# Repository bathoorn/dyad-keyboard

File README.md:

# Dyad

A split keyboard with a rotary encoder ring on each half — a round display
inside the left ring, a circular trackpad inside the right. Custom PCBs in
KiCad, a 3D-printed case, running QMK.

*Dyad: a pair. Two halves, two dials, two boards.*

69 keys, 32 left and 37 right, row-staggered. Bare RP2040 on each side.

---

## The idea that makes it work

"A display on top of a knob" normally means the display rotates, which needs a
slip ring or a wire loom that survives unlimited rotation.

Dyad inverts it. **The display and trackpad are static; the ring rotates around
them.** A fixed centre post rises through the bearing bore and cantilevers the
sensor above the moving parts, so no wire ever moves. Visually and
ergonomically it reads as a knob with a screen on top — electrically it's a
static part with a ring turning beneath it.

Both rings are 50 mm outside diameter, so the halves are a matched pair.

## Hardware

| | |
|---|---|
| MCU | Bare RP2040, one **shared controller module** used by both halves |
| Left pod | GC9A01 1.28" round LCD, 240×240, SPI |
| Right pod | Cirque Pinnacle TM040040, 40 mm |
| Encoders | EC11, driven by a ring gear from the rotating ring |
| Switches | MX hot-swap, Kailh sockets |
| Per-key RGB | SK6812MINI-E — footprints fitted, populated only if wanted |
| Split link | USB-C to USB-C, half-duplex serial |

Four board designs: one controller module (the only board needing an assembly
service), two asymmetric main PCBs, and two knob-module variants.

## Status

| Phase | State |
|---|---|
| 0 — Layout | **Done.** Validated against printed 1:1 mock-ups. |
| 1 — Bench bring-up | **Partial.** Toolchain, flashing, encoder and Cirque all pass. Display, ribbon-SPI, split and current tests await parts. |
| 2 — Knob mechanism | Not started. |
| 3 — KiCad | Main PCBs generated and placed; controller pin assignment and BOM settled. |
| 4 — Case | Not started. Board outlines and plate cutouts exported for it. |

The main PCBs are a **placement scaffold**, not a finished layout. DRC reports
195 violations on the left and 253 on the right, **none** electrical (shorts,
clearance, mask bridges). The 32 and 37 errors are all diode/switch courtyard
overlaps from the deliberate diode-under-switch placement; the rest is
silkscreen. Routing is incomplete, notably the angled thumb keys.

## Repository

```
docs/          PLAN.md, WORKFLOW.md, CONTROLLER.md, PHASE1.md, TOOLS.md,
               GIT.md, plus printable 1:1 mock-ups
hardware/
  interface.yaml   the contract between the PCB and case designs
  layout/          KLE source of truth, parser, pod-placement solver
  pcb-main-*/      the two main PCBs (generated)
  pcb-controller/  controller module, and the vendored RP2040 reference
  outlines/        board outlines, plate cutouts and STEP, for the case
firmware/      QMK external userspace
```

Nearly everything under `hardware/` is **generated** from the KLE layout.
Regenerate with `hardware/generate_main_pcbs.py`, `export_outlines.py` and
`export_plate.py` — see `docs/TOOLS.md` for the environment they need.

## Building the firmware

```bash
qmk config user.qmk_home=~/qmk_firmware
qmk config user.overlay_dir=$PWD/firmware
ln -sfn $PWD/firmware/keyboards/dyad ~/qmk_firmware/keyboards/dyad
qmk compile -kb dyad/split -km default
```

The symlink is required: QMK's external userspace holds keymaps and build
targets, but **not keyboards**.

`dyad/proto` and `dyad/split` are Phase 1 bring-up targets for dev boards, not
the shipping keyboard definition.

## Documentation

- **[PLAN.md](docs/PLAN.md)** — the full design, decisions and rationale
- **[WORKFLOW.md](docs/WORKFLOW.md)** — how the case and PCBs are co-designed
  without deadlocking
- **[CONTROLLER.md](docs/CONTROLLER.md)** — controller pin assignment, BOM and
  build steps
- **[PHASE1.md](docs/PHASE1.md)** — bench bring-up, with results
- **[TOOLS.md](docs/TOOLS.md)** — toolchain, and the traps found in it
- **[GIT.md](docs/GIT.md)** — feature branches, and why KiCad files change how
  git is used here

## Licence

MIT — see [LICENSE](LICENSE).

`hardware/pcb-controller/upstream/` vendors
[RP2040-designguide](https://github.com/calliah333/RP2040-designguide)
(MIT, © 2021 Sleepdealer) as a read-only reference. The key layout originates
from the *Hasukey* KLE layout.

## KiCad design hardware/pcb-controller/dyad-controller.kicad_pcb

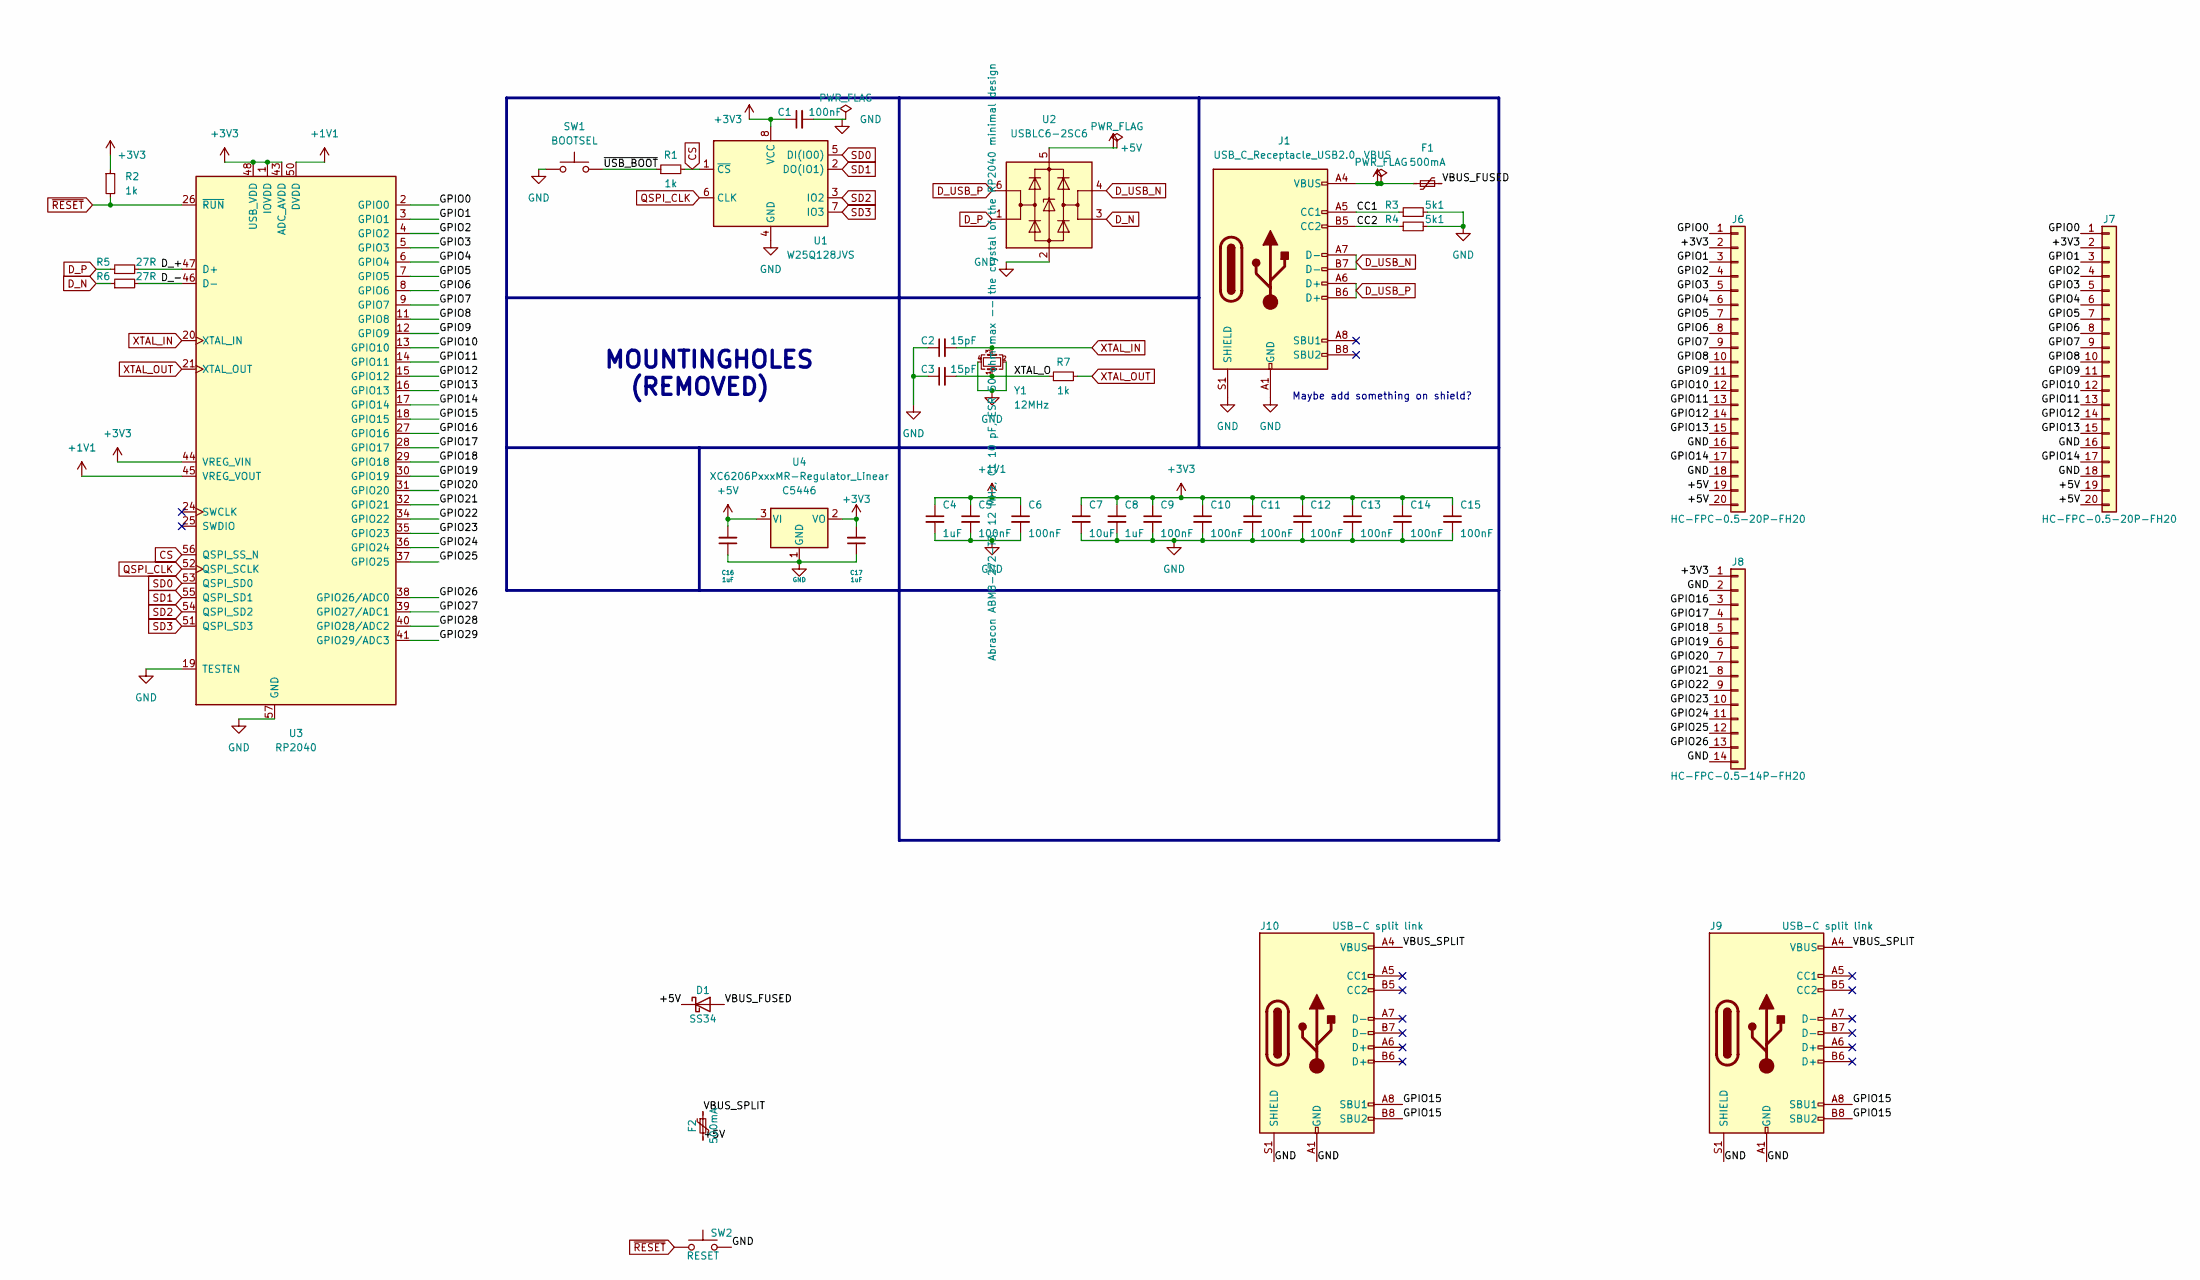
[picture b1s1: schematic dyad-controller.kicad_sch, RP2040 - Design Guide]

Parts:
C1, C5, C6, C9, C10, C11, C12, C13, C14, C15: 100nF; C_0402_1005Metric; LCSC C1525
C2, C3: 15pF; C_0402_1005Metric; LCSC C1548
C4, C8, C16, C17: 1uF; C_0402_1005Metric; LCSC C52923
C7: 10uF; C_0402_1005Metric; LCSC C15525
D1: SS34; D_SMA; LCSC C8678
F1, F2: 500mA; Fuse_1206_3216Metric; LCSC C70076
J1: USB_C_Receptacle_USB2.0; USB_C_Receptacle_HRO_TYPE-C-31-M-12; LCSC C165948
J6, J7: HC-FPC-0.5-20P-FH20; FPC-SMD_20P-P0.50_HC-FPC-0.5-20P-FH20; LCSC C19273932
J8: HC-FPC-0.5-14P-FH20; FPC-SMD_14P-P0.50_HC-FPC-0.5-14P-FH20; LCSC C19273929
J9, J10: USB-C split link; USB_C_Receptacle_HRO_TYPE-C-31-M-12; LCSC C165948
R1, R2, R7: 1k; R_0402_1005Metric; LCSC C11702
R3, R4: 5k1; R_0402_1005Metric; LCSC C25905
R5, R6: 27R; R_0603_1608Metric; LCSC C25190
SW1: BOOTSEL; SW_Push_1P1T_XKB_TS-1187A; LCSC C318884
SW2: RESET; SW_Push_1P1T_XKB_TS-1187A; LCSC C318884
U1: W25Q128JVS; SOIC-8_5.23x5.23mm_P1.27mm; LCSC C131025
U2: USBLC6-2SC6; SOT-23-6; LCSC C2827654
U3: RP2040; RP2040-QFN-56; LCSC C2040
U4: XC6206PxxxMR-Regulator_Linear; SOT-23; LCSC C5446
Y1: 12MHz; Crystal_SMD_3225-4Pin_3.2x2.5mm; LCSC C20625731

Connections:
+1V1: C4.1, C5.1, C6.1, U3.23 (DVDD), U3.45 (VREG_VOUT), U3.50 (DVDD)
+3V3: C1.1, C7.1, C8.1, C9.1, C10.1, C11.1, C12.1, C13.1, C14.1, C15.1, C17.2, J6.2, J7.2, J8.1, R2.1, U1.8 (VCC), U3.1 (IOVDD), U3.10 (IOVDD), U3.22 (IOVDD), U3.33 (IOVDD), U3.42 (IOVDD), U3.43 (ADC_AVDD), U3.44 (VREG_VIN), U3.48 (USB_VDD), U3.49 (IOVDD), U4.2 (VO)
+5V: C16.2, D1.1 (K), F2.2, J6.19, J6.20, J7.19, J7.20, U2.5 (VBUS), U4.3 (VI)
/CC1: J1.A5 (CC1), R3.1
/CC2: J1.B5 (CC2), R4.1
/D_+: R5.2, U3.47 (D+)
/D_-: R6.2, U3.46 (D-)
/GPIO0: J6.1, J7.1, U3.2 (GPIO0)
/GPIO1: J6.3, J7.3, U3.3 (GPIO1)
/GPIO2: J6.4, J7.4, U3.4 (GPIO2)
/GPIO3: J6.5, J7.5, U3.5 (GPIO3)
/GPIO4: J6.6, J7.6, U3.6 (GPIO4)
/GPIO5: J6.7, J7.7, U3.7 (GPIO5)
/GPIO6: J6.8, J7.8, U3.8 (GPIO6)
/GPIO7: J6.9, J7.9, U3.9 (GPIO7)
/GPIO8: J6.10, J7.10, U3.11 (GPIO8)
/GPIO9: J6.11, J7.11, U3.12 (GPIO9)
/GPIO10: J6.12, J7.12, U3.13 (GPIO10)
/GPIO11: J6.13, J7.13, U3.14 (GPIO11)
/GPIO12: J6.14, J7.14, U3.15 (GPIO12)
/GPIO13: J6.15, J7.15, U3.16 (GPIO13)
/GPIO14: J6.17, J7.17, U3.17 (GPIO14)
/GPIO15: J9.A8 (SBU1), J9.B8 (SBU2), J10.A8 (SBU1), J10.B8 (SBU2), U3.18 (GPIO15)
/GPIO16: J8.3, U3.27 (GPIO16)
/GPIO17: J8.4, U3.28 (GPIO17)
/GPIO18: J8.5, U3.29 (GPIO18)
/GPIO19: J8.6, U3.30 (GPIO19)
/GPIO20: J8.7, U3.31 (GPIO20)
/GPIO21: J8.8, U3.32 (GPIO21)
/GPIO22: J8.9, U3.34 (GPIO22)
/GPIO23: J8.10, U3.35 (GPIO23)
/GPIO24: J8.11, U3.36 (GPIO24)
/GPIO25: J8.12, U3.37 (GPIO25)
/GPIO26: J8.13, U3.38 (GPIO26/ADC0)
/GPIO27: U3.39 (GPIO27/ADC1)
/GPIO28: U3.40 (GPIO28/ADC2)
/GPIO29: U3.41 (GPIO29/ADC3)
/VBUS_FUSED: D1.2 (A), F1.2
/VBUS_SPLIT: F2.1, J9.A4 (VBUS), J9.A9 (VBUS), J9.B4 (VBUS), J9.B9 (VBUS), J10.A4 (VBUS), J10.A9 (VBUS), J10.B4 (VBUS), J10.B9 (VBUS)
/XTAL_O: C3.2, R7.1, Y1.1
/~USB_BOOT: R1.1, SW1.2
CS: R1.2, U1.1 (~CS), U3.56 (QSPI_SS_N)
D_N: R6.1, U2.3 (I/O2)
D_P: R5.1, U2.1 (I/O1)
D_USB_N: J1.A7 (D-), J1.B7 (D-), U2.4 (I/O2)
D_USB_P: J1.A6 (D+), J1.B6 (D+), U2.6 (I/O1)
GND: C1.2, C2.1, C3.1, C4.2, C5.2, C6.2, C7.2, C8.2, C9.2, C10.2, C11.2, C12.2, C13.2, C14.2, C15.2, C16.1, C17.1, J1.A1 (GND), J1.A12 (GND), J1.B1 (GND), J1.B12 (GND), J1.S1 (SHIELD), J6.16, J6.18, J7.16, J7.18, J8.2, J8.14, J9.A1 (GND), J9.A12 (GND), J9.B1 (GND), J9.B12 (GND), J9.S1 (SHIELD), J10.A1 (GND), J10.A12 (GND), J10.B1 (GND), J10.B12 (GND), J10.S1 (SHIELD), R3.2, R4.2, SW1.1, SW2.2, U1.4 (GND), U2.2 (GND), U3.19 (TESTEN), U3.57 (GND), U4.1 (GND), Y1.2, Y1.4; also elsewhere on the board
QSPI_CLK: U1.6 (CLK), U3.52 (QSPI_SCLK)
SD0: U1.5 (DI(IO0)), U3.53 (QSPI_SD0)
SD1: U1.2 (DO(IO1)), U3.55 (QSPI_SD1)
SD2: U1.3 (IO2), U3.54 (QSPI_SD2)
SD3: U1.7 (IO3), U3.51 (QSPI_SD3)
VBUS: F1.1, J1.A4 (VBUS), J1.A9 (VBUS), J1.B4 (VBUS), J1.B9 (VBUS)
XTAL_IN: C2.2, U3.20 (XTAL_IN), Y1.3
XTAL_OUT: R7.2, U3.21 (XTAL_OUT)
~RESET: R2.2, SW2.1, U3.26 (~RUN)

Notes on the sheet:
MOUNTINGHOLES (REMOVED)
Maybe add something on shield?

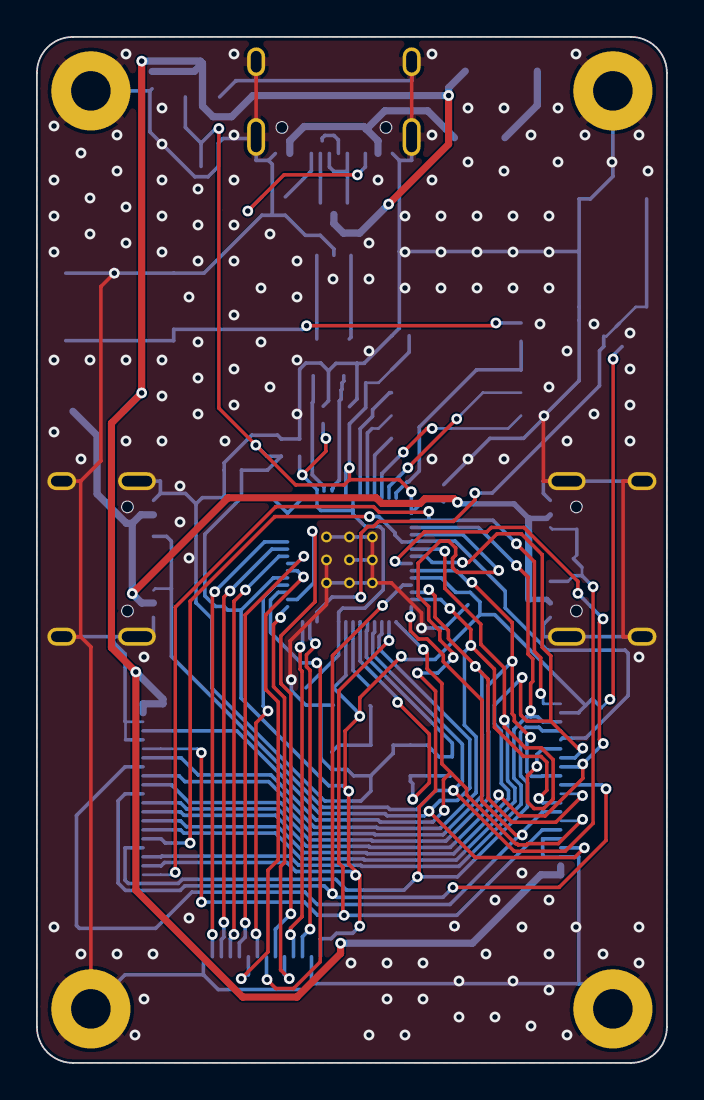
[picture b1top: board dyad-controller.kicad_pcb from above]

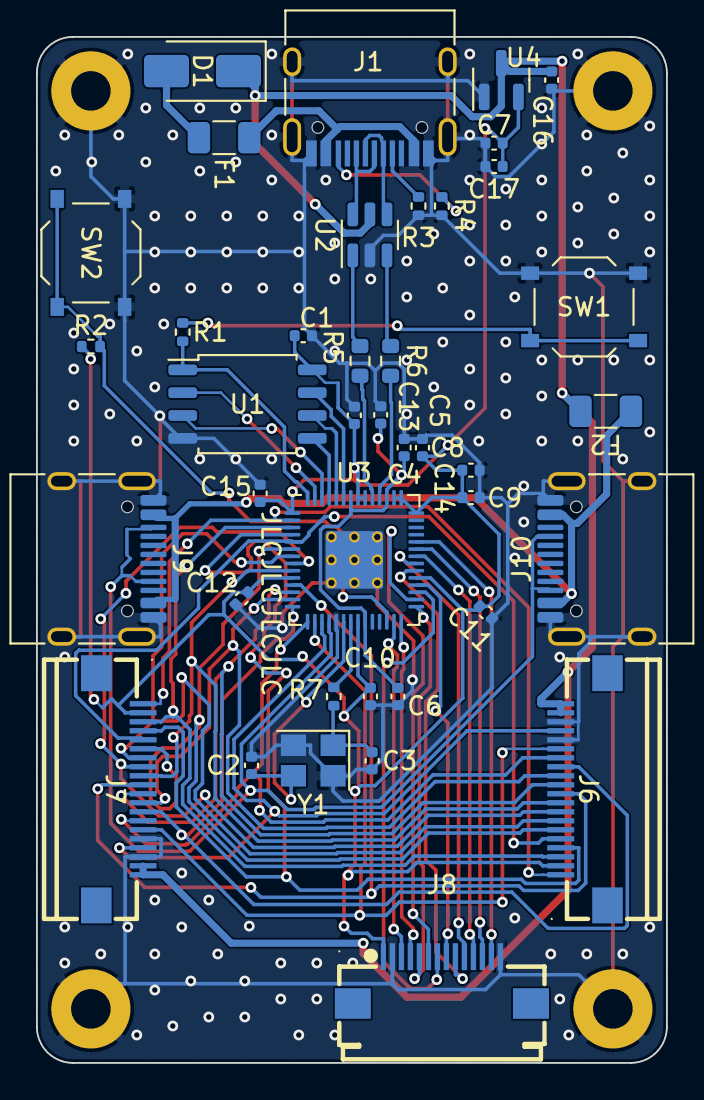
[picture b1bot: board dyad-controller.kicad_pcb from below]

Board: 2 copper layers, 35.0 x 57.0 mm, 44 parts (40 on the bottom side), 53 nets.

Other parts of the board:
H1, H2, H3, H4: MountingHole_2.2mm_M2_Pad

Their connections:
GND: H1.1, H2.1, H3.1, H4.1; also elsewhere on the board

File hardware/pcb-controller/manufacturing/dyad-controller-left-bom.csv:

Comment,Designator,Footprint,LCSC Part #
100nF,"C1,C5,C6,C9,C10,C11,C12,C13,C14,C15",C_0402_1005Metric,C1525
15pF,"C2,C3",C_0402_1005Metric,C1548
1uF,"C4,C8,C16,C17",C_0402_1005Metric,C52923
10uF,C7,C_0402_1005Metric,C15525
SS34,D1,D_SMA,C8678
500mA,"F1,F2",Fuse_1206_3216Metric,C70076
USB_C_Receptacle_USB2.0,J1,USB_C_Receptacle_HRO_TYPE-C-31-M-12,C165948
HC-FPC-0.5-20P-FH20,J6,FPC-SMD_20P-P0.50_HC-FPC-0.5-20P-FH20,C19273932
HC-FPC-0.5-14P-FH20,J8,FPC-SMD_14P-P0.50_HC-FPC-0.5-14P-FH20,C19273929
USB-C split link,J9,USB_C_Receptacle_HRO_TYPE-C-31-M-12,C165948
1k,"R1,R2,R7",R_0402_1005Metric,C11702
5k1,"R3,R4",R_0402_1005Metric,C25905
27R,"R5,R6",R_0603_1608Metric,C25190
BOOTSEL,SW1,SW_Push_1P1T_XKB_TS-1187A,C318884
RESET,SW2,SW_Push_1P1T_XKB_TS-1187A,C318884
W25Q128JVS,U1,SOIC-8_5.23x5.23mm_P1.27mm,C131025
USBLC6-2SC6,U2,SOT-23-6,C2827654
RP2040,U3,RP2040-QFN-56,C2040
XC6206PxxxMR-Regulator_Linear,U4,SOT-23,C5446
12MHz,Y1,Crystal_SMD_3225-4Pin_3.2x2.5mm,C20625731

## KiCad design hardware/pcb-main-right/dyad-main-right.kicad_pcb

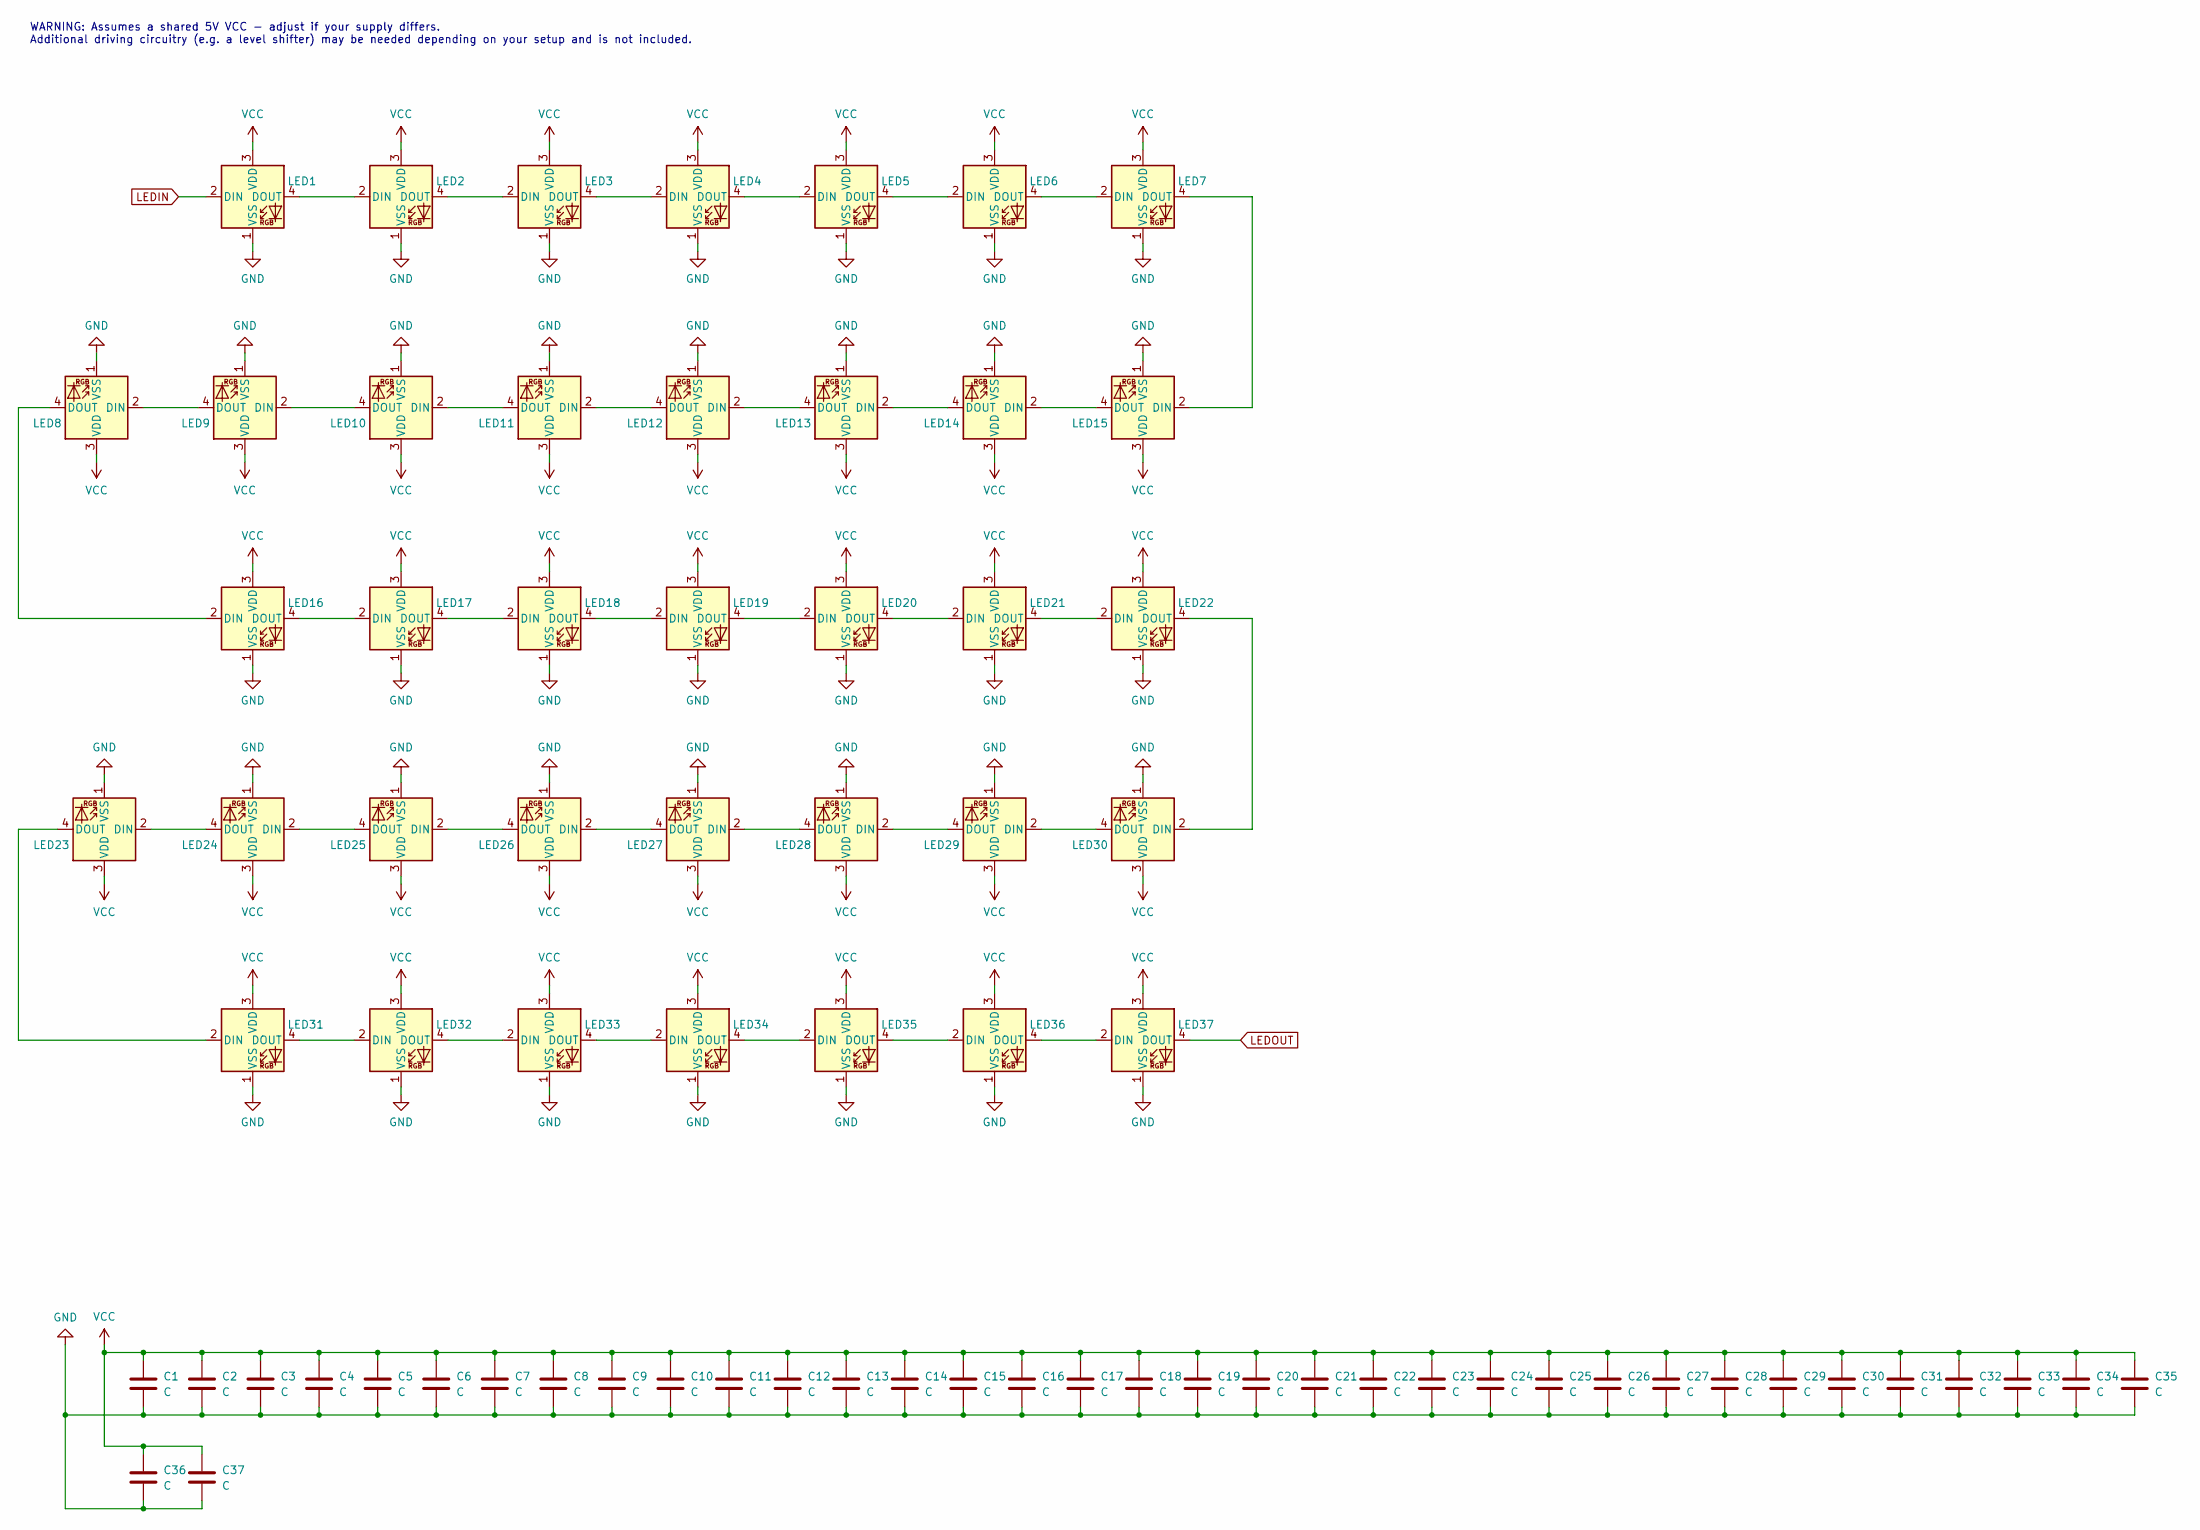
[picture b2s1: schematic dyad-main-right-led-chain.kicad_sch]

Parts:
C1, C2, C3, C4, C5, C6, C7, C8, C9, C10, C11, C12, C13, C14, C15, C16, C17, C18, C19, C20, C21, C22, C23, C24, C25, C26, C27, C28, C29, C30, C31, C32, C33, C34, C35, C36, C37: C; C_0603_1608Metric
LED1, LED2, LED3, LED4, LED5, LED6, LED7, LED8, LED9, LED10, LED11, LED12, LED13, LED14, LED15, LED16, LED17, LED18, LED19, LED20, LED21, LED22, LED23, LED24, LED25, LED26, LED27, LED28, LED29, LED30, LED31, LED32, LED33, LED34, LED35, LED36, LED37: SK6812MINI-E; LED_SK6812MINI-E_3.2x2.8mm_P1.5mm_ReverseMount

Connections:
GND: C1.2, C2.2, C3.2, C4.2, C5.2, C6.2, C7.2, C8.2, C9.2, C10.2, C11.2, C12.2, C13.2, C14.2, C15.2, C16.2, C17.2, C18.2, C19.2, C20.2, C21.2, C22.2, C23.2, C24.2, C25.2, C26.2, C27.2, C28.2, C29.2, C30.2, C31.2, C32.2, C33.2, C34.2, C35.2, C36.2, C37.2, LED1.1 (VSS), LED2.1 (VSS), LED3.1 (VSS), LED4.1 (VSS), LED5.1 (VSS), LED6.1 (VSS), LED7.1 (VSS), LED8.1 (VSS), LED9.1 (VSS), LED10.1 (VSS), LED11.1 (VSS), LED12.1 (VSS), LED13.1 (VSS), LED14.1 (VSS), LED15.1 (VSS), LED16.1 (VSS), LED17.1 (VSS), LED18.1 (VSS), LED19.1 (VSS), LED20.1 (VSS), LED21.1 (VSS), LED22.1 (VSS), LED23.1 (VSS), LED24.1 (VSS), LED25.1 (VSS), LED26.1 (VSS), LED27.1 (VSS), LED28.1 (VSS), LED29.1 (VSS), LED30.1 (VSS), LED31.1 (VSS), LED32.1 (VSS), LED33.1 (VSS), LED34.1 (VSS), LED35.1 (VSS), LED36.1 (VSS), LED37.1 (VSS); also elsewhere on the board
LEDIN: LED1.2 (DIN); also elsewhere on the board
LEDOUT: LED37.4 (DOUT)
unnamed: LED1.4 (DOUT), LED2.2 (DIN)
unnamed: LED2.4 (DOUT), LED3.2 (DIN)
unnamed: LED3.4 (DOUT), LED4.2 (DIN)
unnamed: LED4.4 (DOUT), LED5.2 (DIN)
unnamed: LED5.4 (DOUT), LED6.2 (DIN)
unnamed: LED6.4 (DOUT), LED7.2 (DIN)
unnamed: LED8.2 (DIN), LED9.4 (DOUT)
unnamed: LED10.2 (DIN), LED11.4 (DOUT)
unnamed: LED9.2 (DIN), LED10.4 (DOUT)
unnamed: LED11.2 (DIN), LED12.4 (DOUT)
unnamed: LED12.2 (DIN), LED13.4 (DOUT)
unnamed: LED13.2 (DIN), LED14.4 (DOUT)
unnamed: LED14.2 (DIN), LED15.4 (DOUT)
unnamed: LED7.4 (DOUT), LED15.2 (DIN)
unnamed: LED8.4 (DOUT), LED16.2 (DIN)
unnamed: LED16.4 (DOUT), LED17.2 (DIN)
unnamed: LED17.4 (DOUT), LED18.2 (DIN)
unnamed: LED18.4 (DOUT), LED19.2 (DIN)
unnamed: LED19.4 (DOUT), LED20.2 (DIN)
unnamed: LED20.4 (DOUT), LED21.2 (DIN)
unnamed: LED21.4 (DOUT), LED22.2 (DIN)
unnamed: LED22.4 (DOUT), LED30.2 (DIN)
unnamed: LED23.2 (DIN), LED24.4 (DOUT)
unnamed: LED23.4 (DOUT), LED31.2 (DIN)
unnamed: LED24.2 (DIN), LED25.4 (DOUT)
unnamed: LED25.2 (DIN), LED26.4 (DOUT)
unnamed: LED26.2 (DIN), LED27.4 (DOUT)
unnamed: LED27.2 (DIN), LED28.4 (DOUT)
unnamed: LED28.2 (DIN), LED29.4 (DOUT)
unnamed: LED29.2 (DIN), LED30.4 (DOUT)
unnamed: LED31.4 (DOUT), LED32.2 (DIN)
unnamed: LED32.4 (DOUT), LED33.2 (DIN)
unnamed: LED33.4 (DOUT), LED34.2 (DIN)
unnamed: LED34.4 (DOUT), LED35.2 (DIN)
unnamed: LED35.4 (DOUT), LED36.2 (DIN)
unnamed: LED36.4 (DOUT), LED37.2 (DIN)
VCC: C1.1, C2.1, C3.1, C4.1, C5.1, C6.1, C7.1, C8.1, C9.1, C10.1, C11.1, C12.1, C13.1, C14.1, C15.1, C16.1, C17.1, C18.1, C19.1, C20.1, C21.1, C22.1, C23.1, C24.1, C25.1, C26.1, C27.1, C28.1, C29.1, C30.1, C31.1, C32.1, C33.1, C34.1, C35.1, C36.1, C37.1, LED1.3 (VDD), LED2.3 (VDD), LED3.3 (VDD), LED4.3 (VDD), LED5.3 (VDD), LED6.3 (VDD), LED7.3 (VDD), LED8.3 (VDD), LED9.3 (VDD), LED10.3 (VDD), LED11.3 (VDD), LED12.3 (VDD), LED13.3 (VDD), LED14.3 (VDD), LED15.3 (VDD), LED16.3 (VDD), LED17.3 (VDD), LED18.3 (VDD), LED19.3 (VDD), LED20.3 (VDD), LED21.3 (VDD), LED22.3 (VDD), LED23.3 (VDD), LED24.3 (VDD), LED25.3 (VDD), LED26.3 (VDD), LED27.3 (VDD), LED28.3 (VDD), LED29.3 (VDD), LED30.3 (VDD), LED31.3 (VDD), LED32.3 (VDD), LED33.3 (VDD), LED34.3 (VDD), LED35.3 (VDD), LED36.3 (VDD), LED37.3 (VDD); also elsewhere on the board

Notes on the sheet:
WARNING: Assumes a shared 5V VCC - adjust if your supply differs. Additional driving circuitry (e.g. a level shifter) may be needed depending on your setup and is not included.

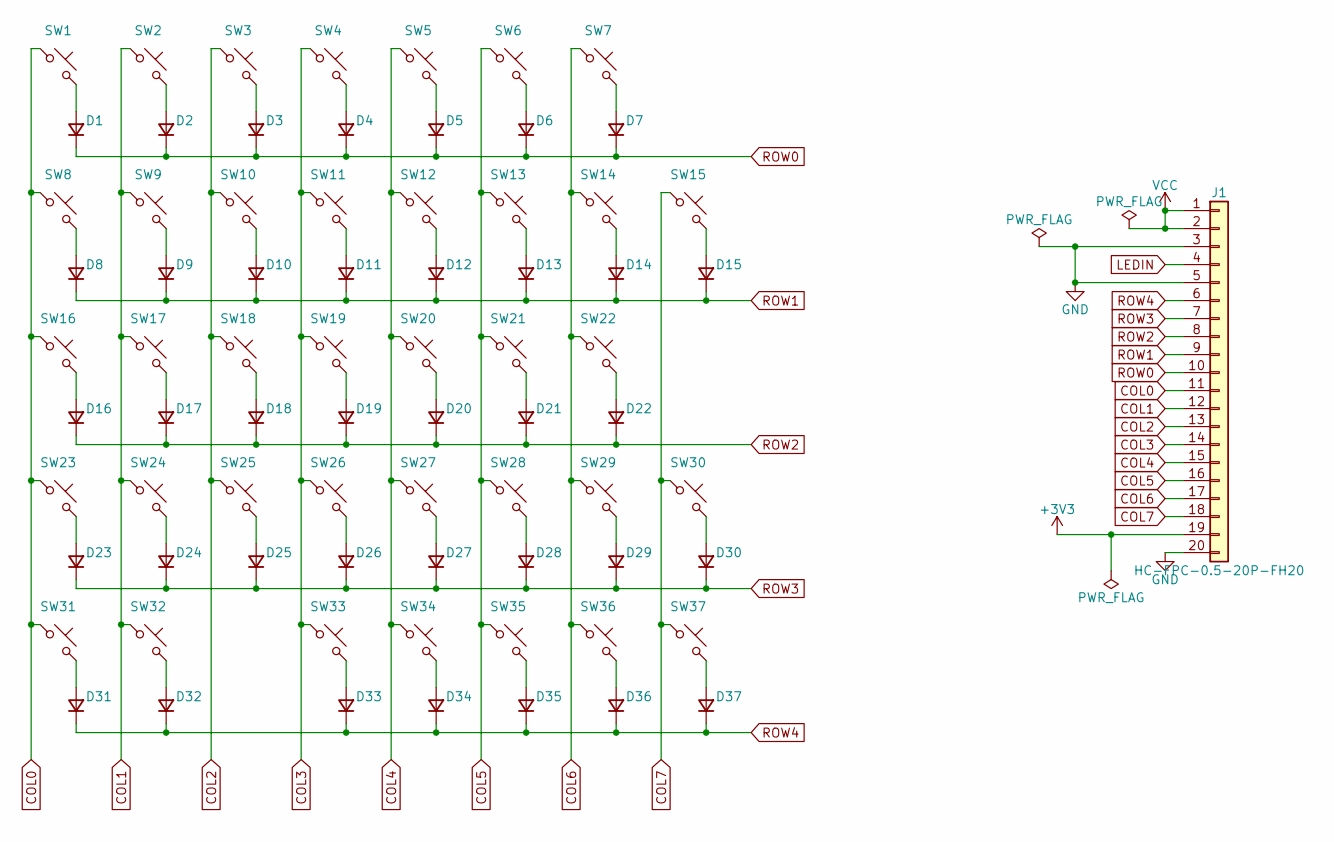
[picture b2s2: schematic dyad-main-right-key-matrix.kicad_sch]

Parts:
D1, D2, D3, D4, D5, D6, D7, D8, D9, D10, D11, D12, D13, D14, D15, D16, D17, D18, D19, D20, D21, D22, D23, D24, D25, D26, D27, D28, D29, D30, D31, D32, D33, D34, D35, D36, D37: D; D_SOD-123
J1: HC-FPC-0.5-20P-FH20; FPC-SMD_20P-P0.50_HC-FPC-0.5-20P-FH20; MPN HC-FPC-0.5-20P-FH20; LCSC C19273932
SW1, SW2, SW3, SW4, SW5, SW6, SW8, SW9, SW10, SW11, SW12, SW13, SW14, SW15, SW16, SW17, SW18, SW19, SW20, SW21, SW23, SW24, SW25, SW26, SW27, SW28, SW29, SW32, SW35, SW36, SW37: SW_Push; SW_MX_HS_CPG151101S11_1u
SW7, SW31: SW_Push; SW_MX_HS_CPG151101S11_1.5u
SW22: SW_Push; SW_MX_HS_CPG151101S11_1.75u
SW30, SW33, SW34: SW_Push; SW_MX_HS_CPG151101S11_1.25u

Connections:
+3V3: J1.19
COL0: J1.11, SW1.1, SW8.1, SW16.1, SW23.1, SW31.1
COL1: J1.12, SW2.1, SW9.1, SW17.1, SW24.1, SW32.1
COL2: J1.13, SW3.1, SW10.1, SW18.1, SW25.1
COL3: J1.14, SW4.1, SW11.1, SW19.1, SW26.1, SW33.1
COL4: J1.15, SW5.1, SW12.1, SW20.1, SW27.1, SW34.1
COL5: J1.16, SW6.1, SW13.1, SW21.1, SW28.1, SW35.1
COL6: J1.17, SW7.1, SW14.1, SW22.1, SW29.1, SW36.1
COL7: J1.18, SW15.1, SW30.1, SW37.1
GND: J1.3, J1.5, J1.20; also elsewhere on the board
LEDIN: J1.4; also elsewhere on the board
unnamed: D1.2 (A), SW1.2
unnamed: D2.2 (A), SW2.2
unnamed: D3.2 (A), SW3.2
unnamed: D4.2 (A), SW4.2
unnamed: D5.2 (A), SW5.2
unnamed: D6.2 (A), SW6.2
unnamed: D7.2 (A), SW7.2
unnamed: D8.2 (A), SW8.2
unnamed: D9.2 (A), SW9.2
unnamed: D10.2 (A), SW10.2
unnamed: D11.2 (A), SW11.2
unnamed: D12.2 (A), SW12.2
unnamed: D13.2 (A), SW13.2
unnamed: D14.2 (A), SW14.2
unnamed: D15.2 (A), SW15.2
unnamed: D16.2 (A), SW16.2
unnamed: D17.2 (A), SW17.2
unnamed: D18.2 (A), SW18.2
unnamed: D19.2 (A), SW19.2
unnamed: D20.2 (A), SW20.2
unnamed: D21.2 (A), SW21.2
unnamed: D22.2 (A), SW22.2
unnamed: D23.2 (A), SW23.2
unnamed: D24.2 (A), SW24.2
unnamed: D25.2 (A), SW25.2
unnamed: D26.2 (A), SW26.2
unnamed: D27.2 (A), SW27.2
unnamed: D28.2 (A), SW28.2
unnamed: D29.2 (A), SW29.2
unnamed: D30.2 (A), SW30.2
unnamed: D31.2 (A), SW31.2
unnamed: D32.2 (A), SW32.2
unnamed: D33.2 (A), SW33.2
unnamed: D34.2 (A), SW34.2
unnamed: D35.2 (A), SW35.2
unnamed: D36.2 (A), SW36.2
unnamed: D37.2 (A), SW37.2
ROW0: D1.1 (K), D2.1 (K), D3.1 (K), D4.1 (K), D5.1 (K), D6.1 (K), D7.1 (K), J1.10
ROW1: D8.1 (K), D9.1 (K), D10.1 (K), D11.1 (K), D12.1 (K), D13.1 (K), D14.1 (K), D15.1 (K), J1.9
ROW2: D16.1 (K), D17.1 (K), D18.1 (K), D19.1 (K), D20.1 (K), D21.1 (K), D22.1 (K), J1.8
ROW3: D23.1 (K), D24.1 (K), D25.1 (K), D26.1 (K), D27.1 (K), D28.1 (K), D29.1 (K), D30.1 (K), J1.7
ROW4: D31.1 (K), D32.1 (K), D33.1 (K), D34.1 (K), D35.1 (K), D36.1 (K), D37.1 (K), J1.6
VCC: J1.1, J1.2; also elsewhere on the board

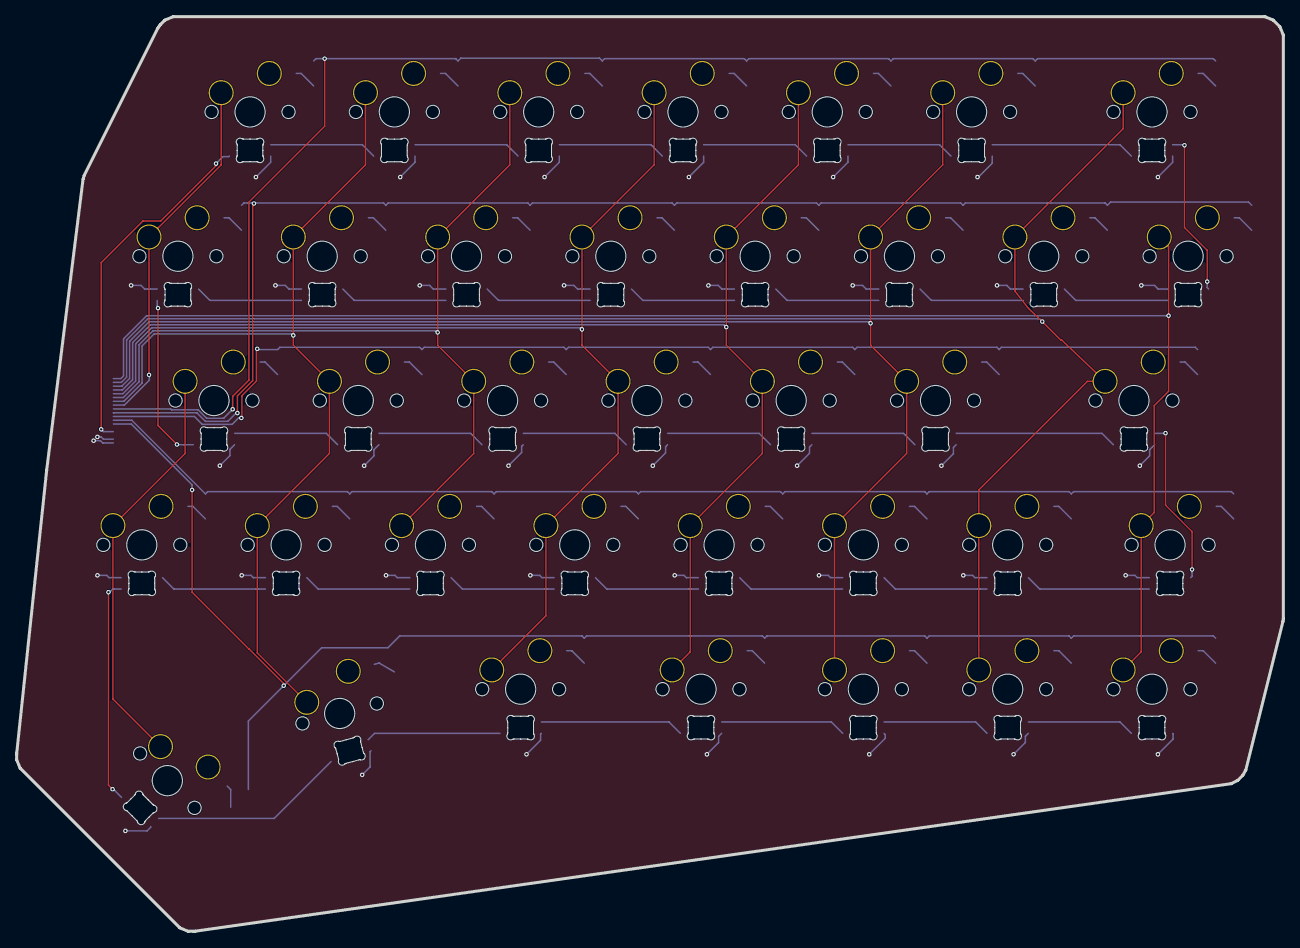
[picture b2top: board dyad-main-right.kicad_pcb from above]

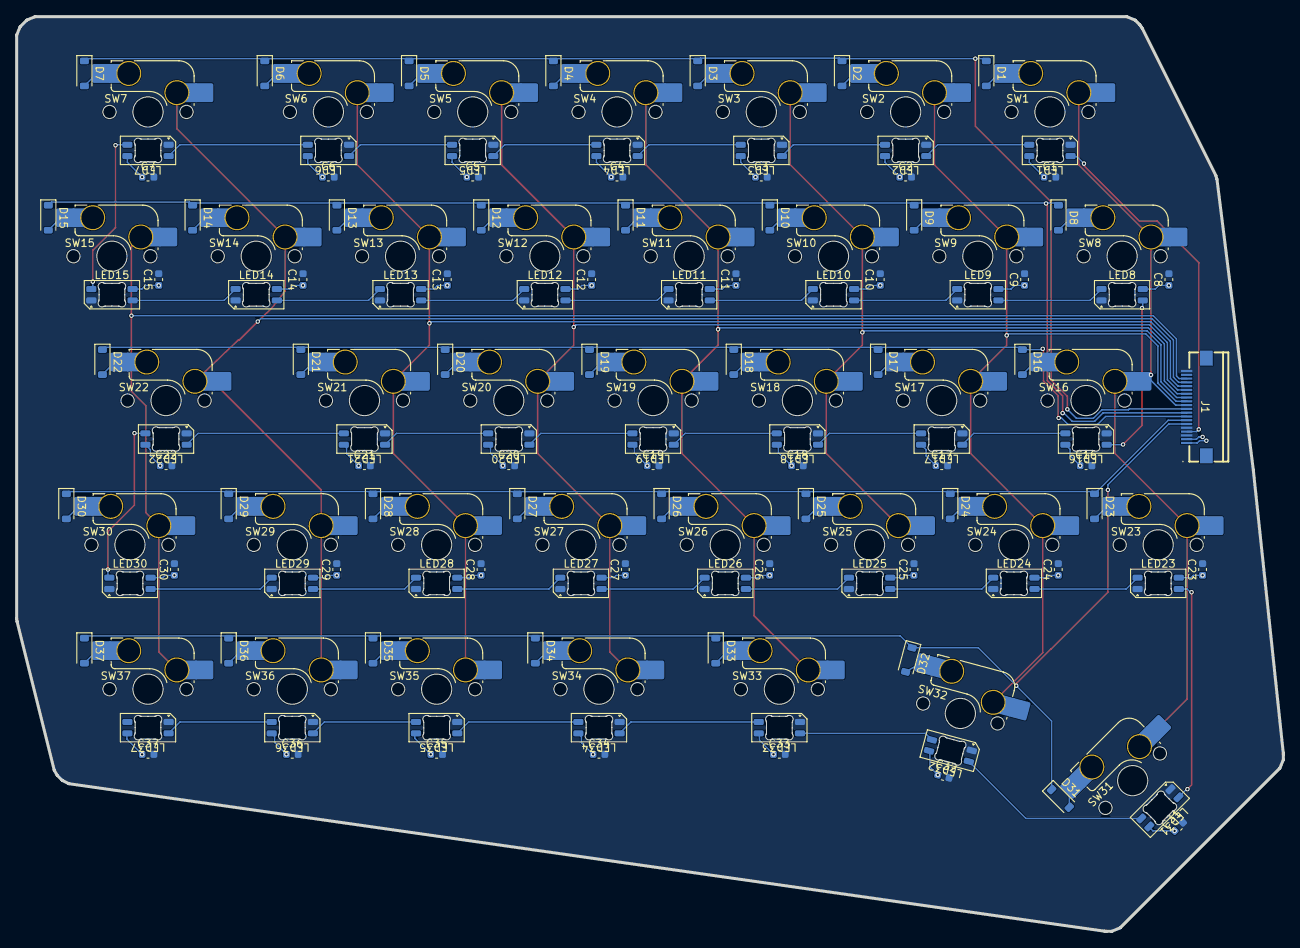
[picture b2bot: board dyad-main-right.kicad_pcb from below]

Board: 2 copper layers, 167.2 x 120.7 mm, 149 parts (149 on the bottom side), 89 nets.
